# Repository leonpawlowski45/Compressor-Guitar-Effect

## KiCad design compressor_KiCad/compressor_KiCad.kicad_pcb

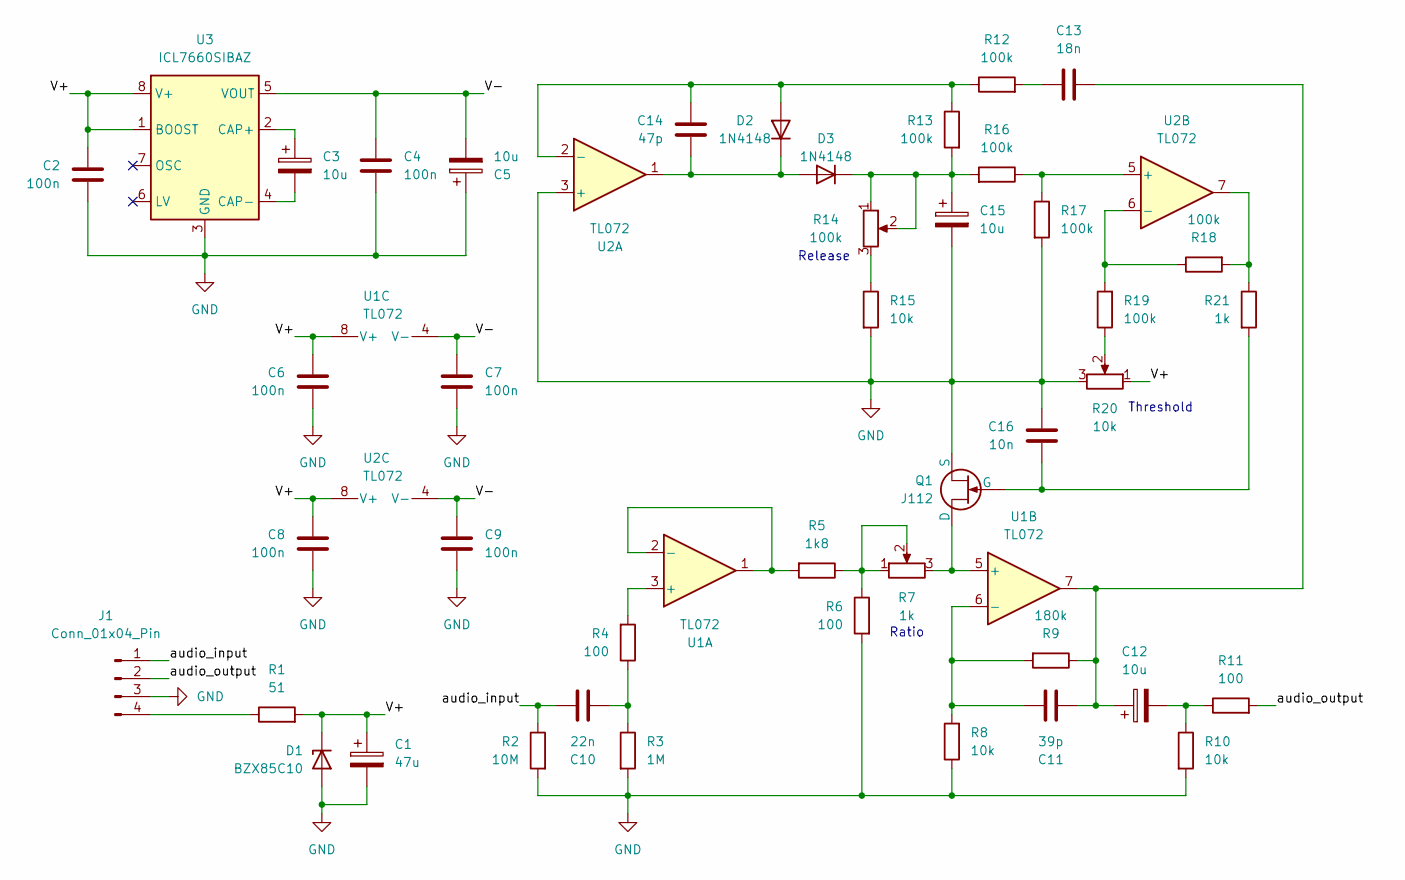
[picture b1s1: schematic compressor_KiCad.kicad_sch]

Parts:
C1: 47u; C_Radial_D5.0mm_H11.0mm_P2.00mm
C2, C4, C6, C7, C8, C9: 100n; C_Disc_D5.0mm_W2.5mm_P5.00mm
C3, C5, C12, C15: 10u; C_Radial_D5.0mm_H11.0mm_P2.00mm
C10: 22n; C_Rect_L18.0mm_W6.0mm_P15.00mm_FKS3_FKP3
C11: 39p; C_Disc_D5.0mm_W2.5mm_P2.50mm
C13: 18n; C_Rect_L13.0mm_W6.0mm_P10.00mm_FKS3_FKP3_MKS4
C14: 47p; C_Disc_D5.1mm_W3.2mm_P5.00mm
C16: 10n; C_Rect_L13.0mm_W5.0mm_P10.00mm_FKS3_FKP3_MKS4
D1: BZX85C10; D_DO-41_SOD81_P7.62mm_Horizontal
D2, D3: 1N4148; D_DO-35_SOD27_P7.62mm_Horizontal
J1: Conn_01x04_Pin; PinHeader_1x04_P2.54mm_Vertical
Q1: J112; TO-92L_Inline_Wide
R1: 51; R_Axial_DIN0207_L6.3mm_D2.5mm_P10.16mm_Horizontal
R2: 10M; R_Axial_DIN0207_L6.3mm_D2.5mm_P10.16mm_Horizontal
R3: 1M; R_Axial_DIN0207_L6.3mm_D2.5mm_P10.16mm_Horizontal
R4, R6, R11: 100; R_Axial_DIN0207_L6.3mm_D2.5mm_P10.16mm_Horizontal
R5: 1k8; R_Axial_DIN0207_L6.3mm_D2.5mm_P10.16mm_Horizontal
R7: 1k; PinHeader_1x03_P2.54mm_Vertical
R8, R10, R15: 10k; R_Axial_DIN0207_L6.3mm_D2.5mm_P10.16mm_Horizontal
R9: 180k; R_Axial_DIN0207_L6.3mm_D2.5mm_P10.16mm_Horizontal
R12, R13, R16, R17, R18, R19: 100k; R_Axial_DIN0207_L6.3mm_D2.5mm_P10.16mm_Horizontal
R14: 100k; PinHeader_1x03_P2.54mm_Vertical
R20: 10k; PinHeader_1x03_P2.54mm_Vertical
R21: 1k; R_Axial_DIN0207_L6.3mm_D2.5mm_P10.16mm_Horizontal
U1, U2: TL072; DIP-8_W7.62mm
U3: ICL7660SIBAZ; SOIC-8_3.9x4.9mm_P1.27mm

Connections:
/V+: C1.1, C2.1, C6.1, C8.1, D1.1 (K), R1.2, R20.1, U1.8 (V+), U2.8 (V+), U3.1 (BOOST), U3.8 (V+)
/V-: C4.1, C5.2, C7.1, C9.1, U1.4 (V-), U2.4 (V-), U3.5 (VOUT)
/audio_input: C10.1, J1.1, R2.1
/audio_output: J1.2, R11.2
GND: C1.2, C2.2, C4.2, C5.1, C6.2, C7.2, C8.2, C9.2, C15.2, C16.1, D1.2 (A), J1.3, Q1.2 (S), R2.2, R3.2, R6.2, R8.1, R10.2, R15.2, R17.2, R20.3, U2.3 (+), U3.3 (GND)
unnamed: C10.2, R3.1, R4.1
unnamed: C11.2, C12.1, C13.1, R9.1, U1.7
unnamed: C12.2, R10.1, R11.1
unnamed: C13.2, R12.2
unnamed: C14.1, D2.2 (A), R12.1, R13.1, U2.2 (-)
unnamed: C14.2, D2.1 (K), D3.2 (A), U2.1
unnamed: C15.1, D3.1 (K), R13.2, R14.1, R14.2, R16.2
unnamed: J1.4, R1.1
unnamed: Q1.1 (D), R7.3, U1.5 (+)
unnamed: C16.2, Q1.3 (G), R21.2
unnamed: R5.1, R6.1, R7.1, R7.2
unnamed: R14.3, R15.1
unnamed: R18.2, R21.1, U2.7
unnamed: R19.1, R20.2
unnamed: R4.2, U1.3 (+)
unnamed: R5.2, U1.1, U1.2 (-)
unnamed: C11.1, R8.2, R9.2, U1.6 (-)
unnamed: R16.1, R17.1, U2.5 (+)
unnamed: R18.1, R19.2, U2.6 (-)
unnamed: C3.1, U3.2 (CAP+)
unnamed: C3.2, U3.4 (CAP-)

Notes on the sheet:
Release
Threshold
Ratio

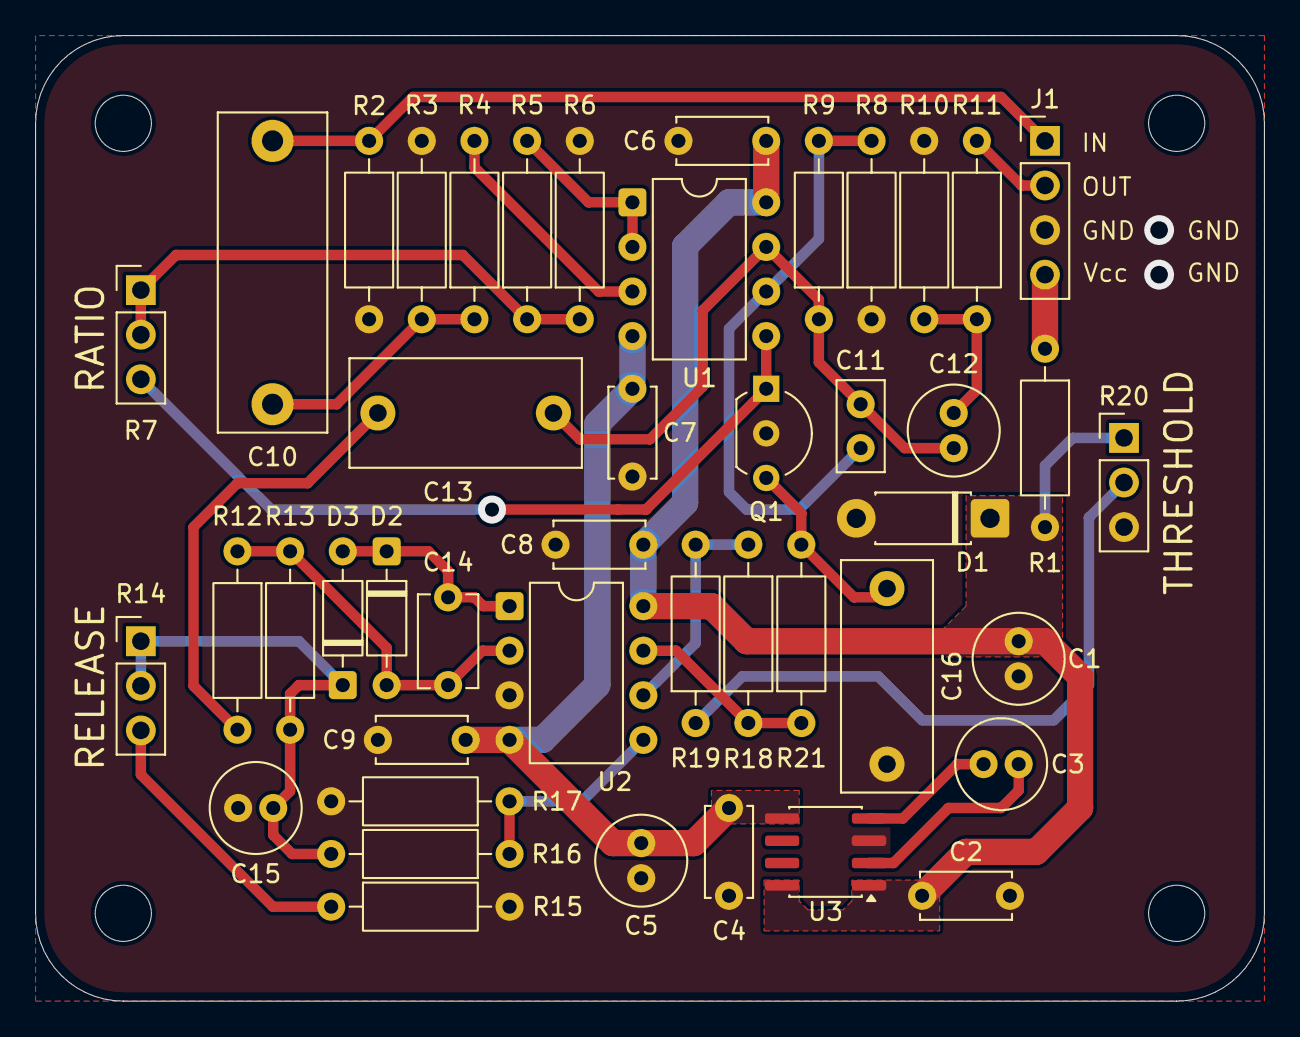
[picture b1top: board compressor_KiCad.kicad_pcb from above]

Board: 2 copper layers, 70.0 x 55.0 mm, 49 parts (0 on the bottom side), 26 nets.

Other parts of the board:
M3, M3#2, M3#3, M3#4: MountingHole_3.2mm_M3_ISO14580

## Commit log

2026-06-23 Add KiCad schematic and PCB design
2026-06-23 Add LTSpice circuit simulation
